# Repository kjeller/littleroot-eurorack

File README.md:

# littleroot-eurorack
Littleroot is a 3U  X HP Eurorack modular synth.

TODO Image of modular

# Modules

TODO no modules yet :(

# Chassi and power supply

| Description  | Category | Link     |
|--------------|----------|----------|
| MIAW Power supply | PSU |  [Link](bus_board/README.md) |
| Littleroot bus board | Bus board |  [Link](bus_board/README.md) |
| Case sidepanel | Case | [Link](https://www.thingiverse.com/thing:4768191)  |

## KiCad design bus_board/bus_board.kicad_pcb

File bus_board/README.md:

# Littleroot bus board

A 12 slot eurorack module bus board.

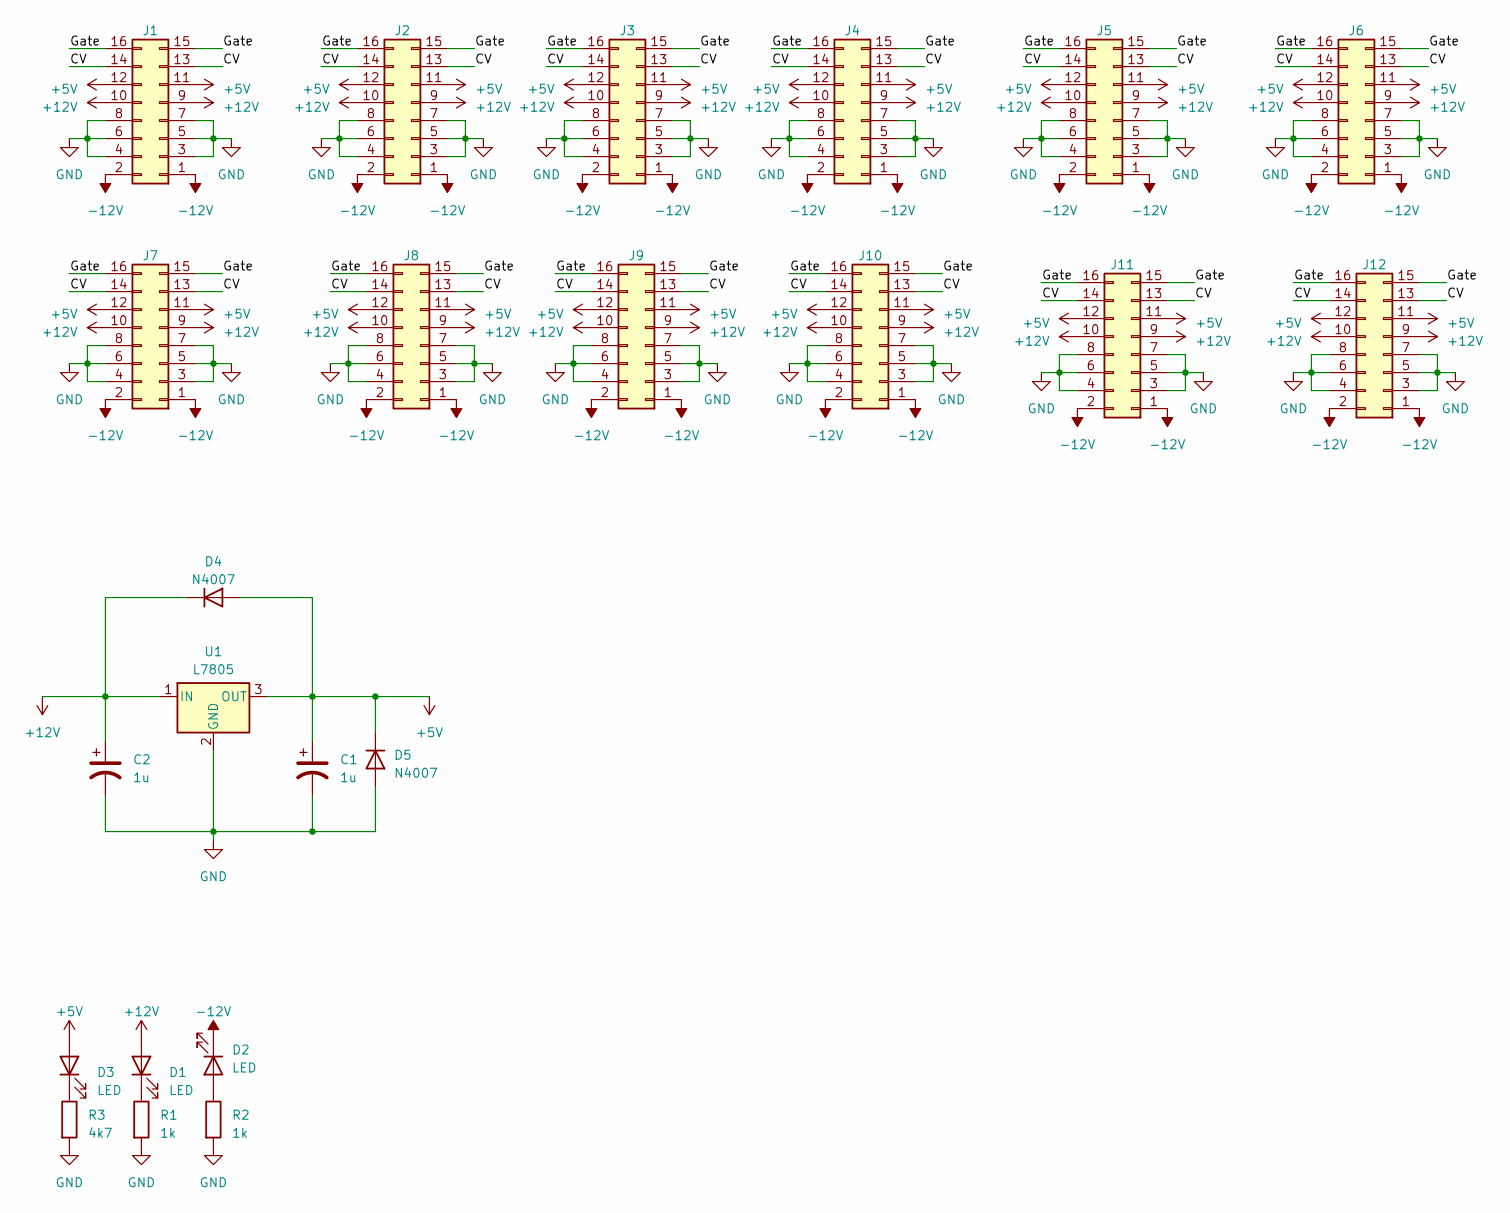
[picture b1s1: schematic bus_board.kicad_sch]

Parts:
C1, C2: 1u; CP_Radial_D10.0mm_P3.80mm
D1, D2, D3: LED; D_DO-35_SOD27_P2.54mm_Vertical_AnodeUp
D4, D5: N4007; D_DO-15_P12.70mm_Horizontal
J1, J2, J3, J4, J5, J6, J7, J8, J9, J10, J11, J12: IDC-Header_2x08_P2.54mm_Vertical
R1, R2: 1k; R_Axial_DIN0309_L9.0mm_D3.2mm_P15.24mm_Horizontal
R3: 4k7; R_Axial_DIN0309_L9.0mm_D3.2mm_P15.24mm_Horizontal
U1: L7805; TO-220-3_Vertical

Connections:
+5V: C1.1, D3.2 (A), D4.2 (A), D5.1 (K), J1.11, J1.12, J2.11, J2.12, J3.11, J3.12, J4.11, J4.12, J5.11, J5.12, J6.11, J6.12, J7.11, J7.12, J8.11, J8.12, J9.11, J9.12, J10.11, J10.12, J11.11, J11.12, J12.11, J12.12, U1.3 (OUT)
+12V: C2.1, D1.2 (A), D4.1 (K), J1.9, J1.10, J2.9, J2.10, J3.9, J3.10, J4.9, J4.10, J5.9, J5.10, J6.9, J6.10, J7.9, J7.10, J8.9, J8.10, J9.9, J9.10, J10.9, J10.10, J11.9, J11.10, J12.9, J12.10, U1.1 (IN)
-12V: D2.1 (K), J1.1, J1.2, J2.1, J2.2, J3.1, J3.2, J4.1, J4.2, J5.1, J5.2, J6.1, J6.2, J7.1, J7.2, J8.1, J8.2, J9.1, J9.2, J10.1, J10.2, J11.1, J11.2, J12.1, J12.2
/CV: J1.13, J1.14, J2.13, J2.14, J3.13, J3.14, J4.13, J4.14, J5.13, J5.14, J6.13, J6.14, J7.13, J7.14, J8.13, J8.14, J9.13, J9.14, J10.13, J10.14, J11.13, J11.14, J12.13, J12.14
/Gate: J1.15, J1.16, J2.15, J2.16, J3.15, J3.16, J4.15, J4.16, J5.15, J5.16, J6.15, J6.16, J7.15, J7.16, J8.15, J8.16, J9.15, J9.16, J10.15, J10.16, J11.15, J11.16, J12.15, J12.16
GND: C1.2, C2.2, D5.2 (A), J1.3, J1.4, J1.5, J1.6, J1.7, J1.8, J2.3, J2.4, J2.5, J2.6, J2.7, J2.8, J3.3, J3.4, J3.5, J3.6, J3.7, J3.8, J4.3, J4.4, J4.5, J4.6, J4.7, J4.8, J5.3, J5.4, J5.5, J5.6, J5.7, J5.8, J6.3, J6.4, J6.5, J6.6, J6.7, J6.8, J7.3, J7.4, J7.5, J7.6, J7.7, J7.8, J8.3, J8.4, J8.5, J8.6, J8.7, J8.8, J9.3, J9.4, J9.5, J9.6, J9.7, J9.8, J10.3, J10.4, J10.5, J10.6, J10.7, J10.8, J11.3, J11.4, J11.5, J11.6, J11.7, J11.8, J12.3, J12.4, J12.5, J12.6, J12.7, J12.8, R1.2, R2.2, R3.2, U1.2 (GND)
unnamed: D1.1 (K), R1.1
unnamed: D2.2 (A), R2.1
unnamed: D3.1 (K), R3.1

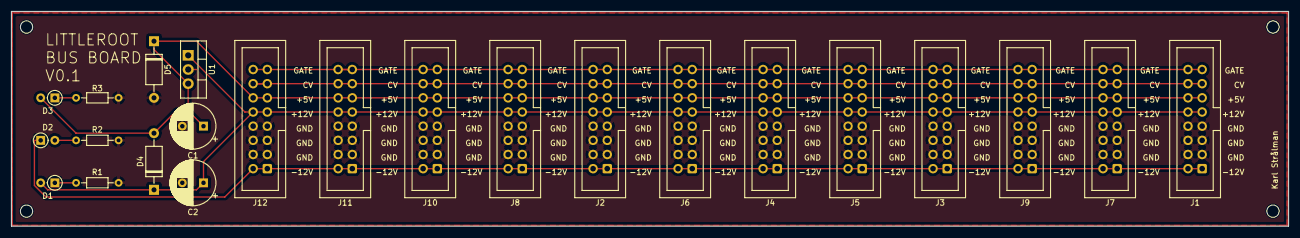
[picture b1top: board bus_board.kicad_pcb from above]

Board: 2 copper layers, 229.0 x 38.5 mm, 23 parts (0 on the bottom side), 9 nets.

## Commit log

2023-04-10 Add kicad gitignores
2023-04-10 Add first draft version of bus board
2023-04-10 Initial readme with info
